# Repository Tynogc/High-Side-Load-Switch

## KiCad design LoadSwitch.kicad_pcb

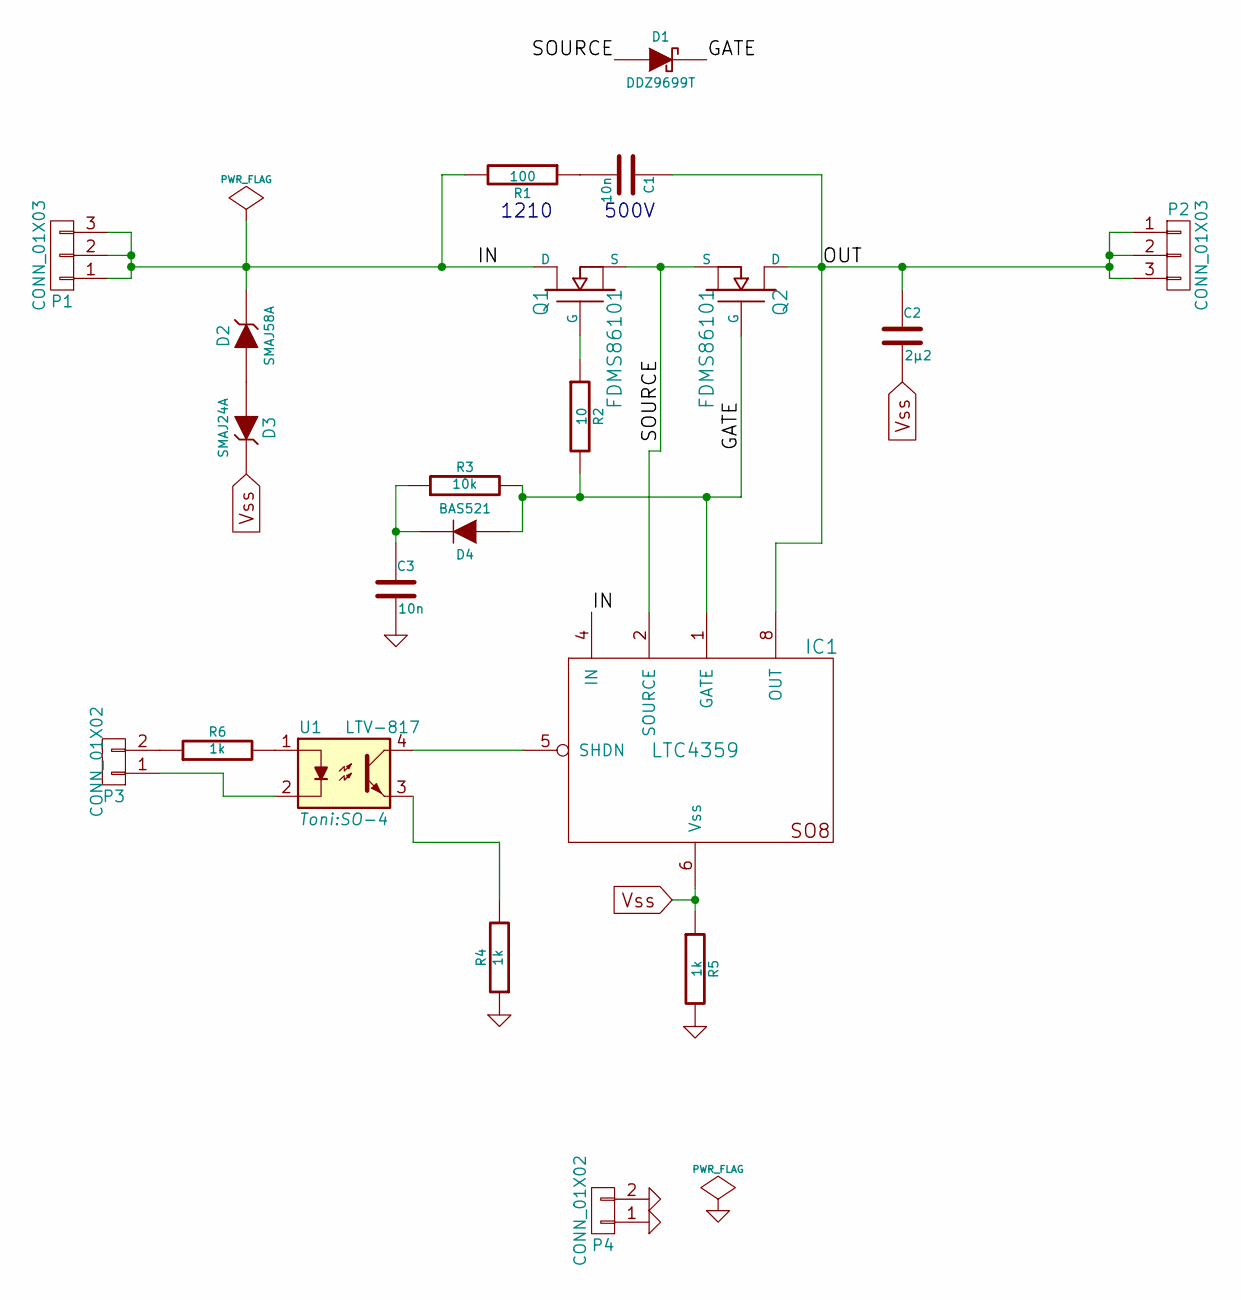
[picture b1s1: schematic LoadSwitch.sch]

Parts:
C1: 10n; C_1210_HandSoldering
C2: 2µ2; C_0805
C3: 10n; C_0805
D1: DDZ9699T; SOD-523
D2: SMAJ58A; SMA-SMB_Universal_Handsoldering
D3: SMAJ24A; SMA-SMB_Universal_Handsoldering
D4: BAS521; SOD-523
IC1: LTC4359; MSOP-8_power_pad
P1, P2: CONN_01X03; Pin_Header_Angled_1x05
P3, P4: CONN_01X02; Pin_Header_Angled_1x03
Q1, Q2: FDMS86101; SO8_WITH_EP
R1: 100; R_1210_HandSoldering
R2: 10; R_0603_HandSoldering
R3: 10k; R_0603_HandSoldering
R4, R5, R6: 1k; R_0603_HandSoldering
U1: LTV-817; SO-4

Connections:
/GATE: D1.2 (K), D4.1 (A), IC1.1 (GATE), Q2.G, R2.2, R3.2
/IN: D2.2 (K), IC1.4 (IN), P1.1, P1.2, P1.3, Q1.D, R1.2
/OUT: C1.1, C2.1, IC1.8 (OUT), P2.1, P2.2, P2.3, Q2.D
/SOURCE: D1.1 (A), IC1.2 (SOURCE), Q1.S, Q2.S
GND: C3.2, P4.1, P4.2, R4.1, R5.2
unnamed: C1.2, R1.1
unnamed: C3.1, D4.2 (K), R3.1
unnamed: D2.1 (A), D3.1 (A)
unnamed: IC1.5 (SHDN), U1.4
unnamed: P3.1, U1.2
unnamed: P3.2, R6.1
unnamed: Q1.G, R2.1
unnamed: R4.2, U1.3
unnamed: R6.2, U1.1
Vss: C2.2, D3.2 (K), IC1.6 (Vss), IC1.9, R5.1

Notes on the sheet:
1210
500V

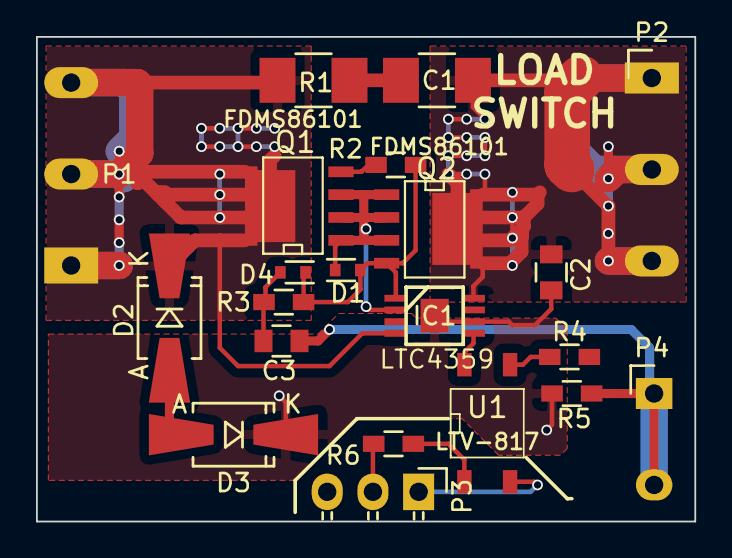
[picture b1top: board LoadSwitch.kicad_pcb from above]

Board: 2 copper layers, 36.6 x 26.9 mm, 21 parts (0 on the bottom side), 15 nets.

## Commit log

2015-11-18 Initialcommit
2015-11-21 Create Spezifikation
2015-11-21 Update Spezifikation
2015-12-01 Korrekte Ansteuerung des SHDN pins
2015-12-01 Pads auf Solid gesetzt
2015-12-04 Bestückungsdruck geändert.
2015-12-04 Gerber erstellt
